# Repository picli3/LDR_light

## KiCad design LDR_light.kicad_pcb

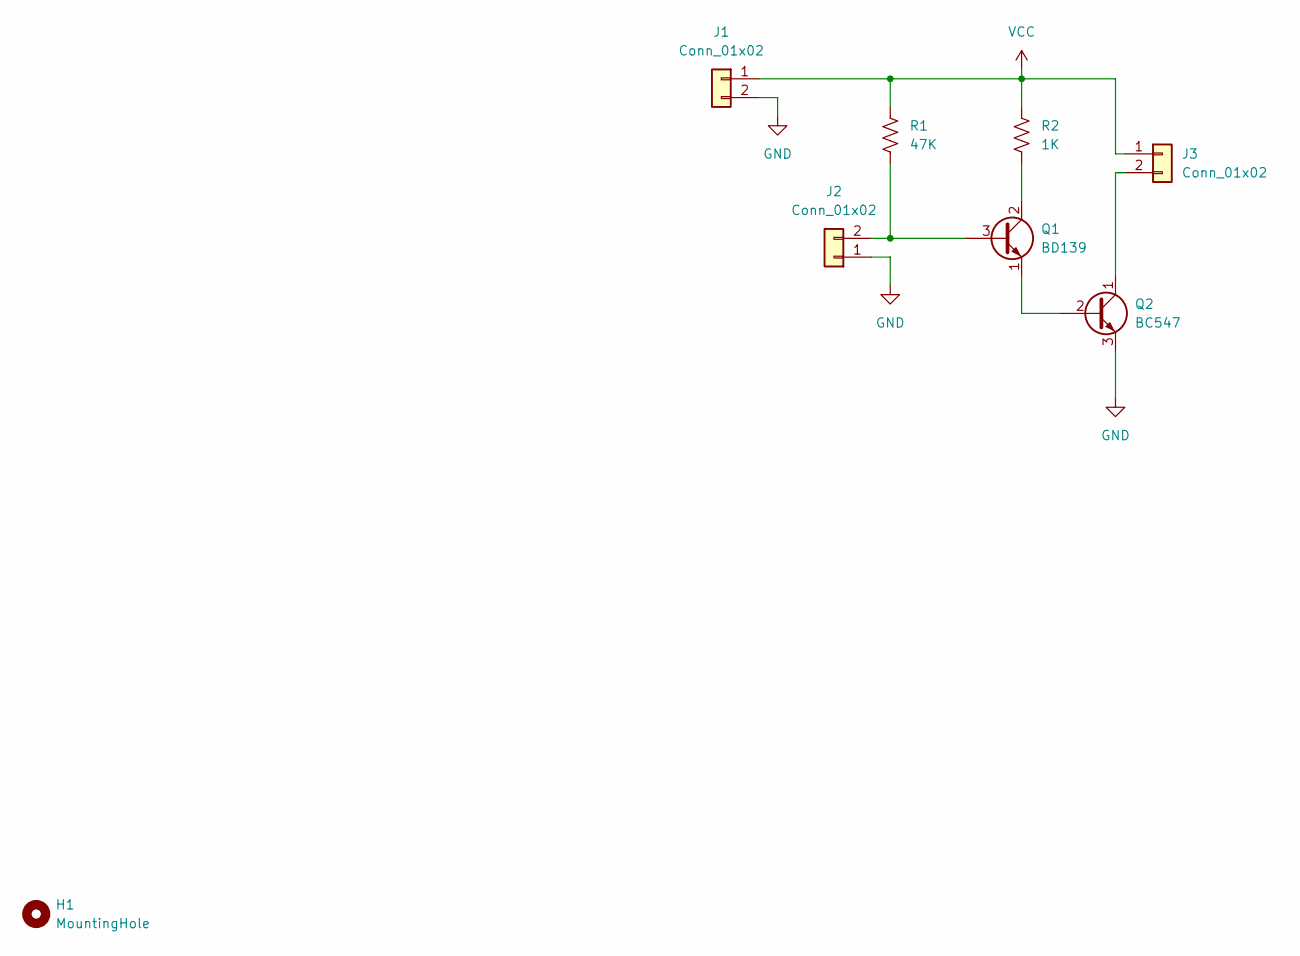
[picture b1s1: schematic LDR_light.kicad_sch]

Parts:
H1: MountingHole; MountingHole_3.2mm_M3
J1, J2, J3: Conn_01x02; TerminalBlock_bornier-2_P5.08mm
Q1: BD139; TO-126-3_Vertical
Q2: BC547; TO-92L_Inline_Wide
R1: 47K; R_Axial_DIN0309_L9.0mm_D3.2mm_P12.70mm_Horizontal
R2: 1K; R_Axial_DIN0309_L9.0mm_D3.2mm_P12.70mm_Horizontal

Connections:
GND: J1.2, J2.1, Q2.3 (E)
unnamed: J2.2, Q1.3 (B), R1.2
unnamed: J3.2, Q2.1 (C)
unnamed: Q1.1 (E), Q2.2 (B)
unnamed: Q1.2 (C), R2.2
VCC: J1.1, J3.1, R1.1, R2.1

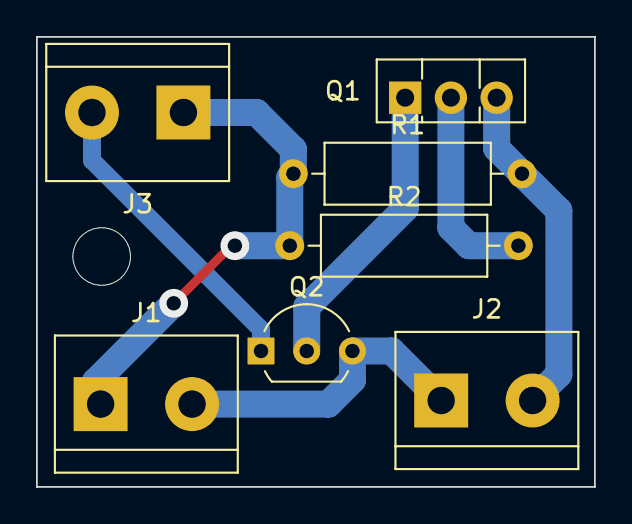
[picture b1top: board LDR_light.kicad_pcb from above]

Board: 2 copper layers, 31.0 x 25.0 mm, 8 parts (0 on the bottom side), 6 nets.

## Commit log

2023-02-19 circuito terminado
